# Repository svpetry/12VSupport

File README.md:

# 12VSupport
System to support a vehicle 12V electrical system with a LiIon battery to prevent the lead battery from depletion.

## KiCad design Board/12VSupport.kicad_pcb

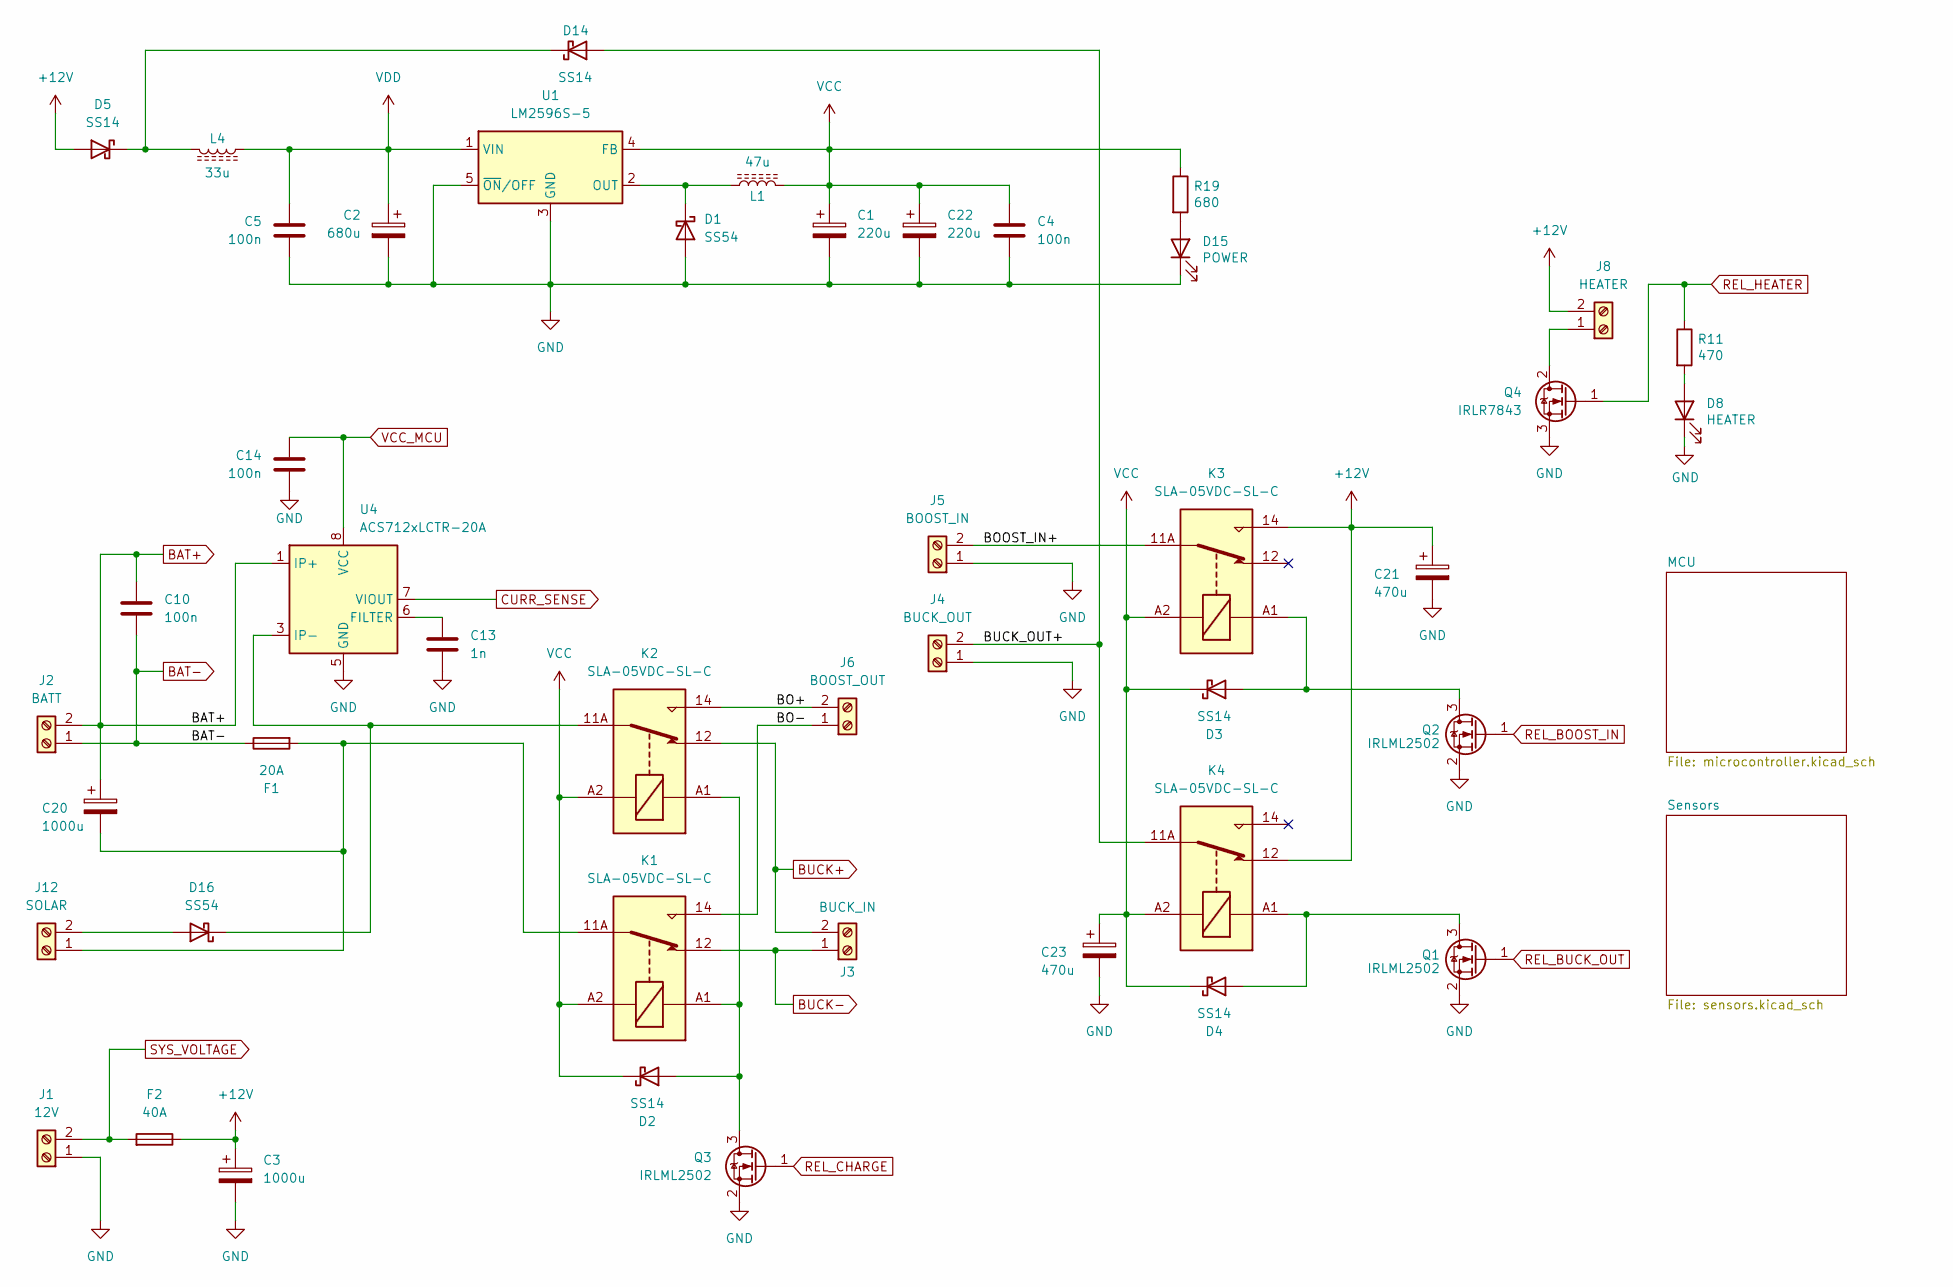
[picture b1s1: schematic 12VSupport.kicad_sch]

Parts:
C1, C22: 220u; CP_Radial_D6.3mm_P2.50mm
C2: 680u; CP_Radial_D10.0mm_P5.00mm
C3, C20: 1000u; CP_Radial_D13.0mm_P5.00mm
C4, C5, C10, C14: 100n; C_0805_2012Metric
C13: 1n; C_0805_2012Metric
C21: 470u; CP_Radial_D10.0mm_P5.00mm
C23: 470u; CP_Radial_D8.0mm_P3.80mm
D1, D16: SS54; D_SMB
D2, D3, D4, D5, D14: SS14; D_SMA
D8: HEATER; LED_0805_2012Metric
D15: POWER; LED_0805_2012Metric
F1: 20A; Fuseholder_Blade
F2: 40A; Fuseholder_Blade
J1: 12V; KF7.62_2P
J2: BATT; KF7.62_2P
J3: BUCK_IN; KF7.62_2P
J4: BUCK_OUT; KF7.62_2P
J5: BOOST_IN; KF7.62_2P
J6: BOOST_OUT; KF7.62_2P
J8: HEATER; TerminalBlock_Altech_AK300-2_P5.00mm
J12: SOLAR; TerminalBlock_Altech_AK300-2_P5.00mm
K1, K2, K3, K4: SLA-05VDC-SL-C; Relay_SPDT_RAYEX-L90
L1: 47u; L_12x12mm_H6mm
L4: 33u; L_10.4x10.4_H4.8
Q1, Q2, Q3: IRLML2502; SOT-23
Q4: IRLR7843; TO-252-2
R11: 470; R_0805_2012Metric
R19: 680; R_0805_2012Metric
U1: LM2596S-5; TO-263-5_TabPin3
U4: ACS712xLCTR-20A; SOIC-8_3.9x4.9mm_P1.27mm

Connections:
+12V: C3.1, C21.1, D5.2 (A), F2.1, J8.2, K3.14, K4.12
/BO+: J6.2, K2.14
/BO-: J6.1, K1.14
/BOOST_IN+: J5.2, K3.11A, K3.11B
/BUCK_OUT+: D14.2 (A), J4.2, K4.11A, K4.11B
BAT+: C10.1, C20.1, J2.2, U4.1 (IP+), U4.2 (IP+); also elsewhere on the board
BAT-: C10.2, F1.1, J2.1; also elsewhere on the board
BUCK+: J3.2, K2.12
BUCK-: J3.1, K1.12
CURR_SENSE: U4.7 (VIOUT); also elsewhere on the board
GND: C1.2, C2.2, C3.2, C4.2, C5.2, C13.2, C14.2, C21.2, C22.2, C23.2, D1.2 (A), D8.1 (K), D15.1 (K), J1.1, J4.1, J5.1, Q1.2 (S), Q2.2 (S), Q3.2 (S), Q4.3 (S), U1.3 (GND), U1.5 (~ON/OFF), U4.5 (GND); also elsewhere on the board
unnamed: D1.1 (K), L1.1, U1.2 (OUT)
unnamed: D2.2 (A), K1.A1, K2.A1, Q3.3 (D)
unnamed: D3.2 (A), K3.A1, Q2.3 (D)
unnamed: D4.2 (A), K4.A1, Q1.3 (D)
unnamed: D8.2 (A), R11.2
unnamed: D5.1 (K), D14.1 (K), L4.2
unnamed: D15.2 (A), R19.2
unnamed: D16.2 (A), J12.2
unnamed: D16.1 (K), K2.11A, K2.11B, U4.3 (IP-), U4.4 (IP-)
unnamed: J8.1, Q4.2 (D)
unnamed: C20.2, F1.2, J12.1, K1.11A, K1.11B
unnamed: C13.1, U4.6 (FILTER)
REL_BOOST_IN: Q2.1 (G); also elsewhere on the board
REL_BUCK_OUT: Q1.1 (G); also elsewhere on the board
REL_CHARGE: Q3.1 (G); also elsewhere on the board
REL_HEATER: Q4.1 (G), R11.1; also elsewhere on the board
SYS_VOLTAGE: F2.2, J1.2; also elsewhere on the board
VCC: C1.1, C4.1, C22.1, C23.1, D2.1 (K), D3.1 (K), D4.1 (K), K1.A2, K2.A2, K3.A2, K4.A2, L1.2, R19.1, U1.4 (FB); also elsewhere on the board
VCC_MCU: C14.1, U4.8 (VCC); also elsewhere on the board
VDD: C2.1, C5.1, L4.1, U1.1 (VIN); also elsewhere on the board

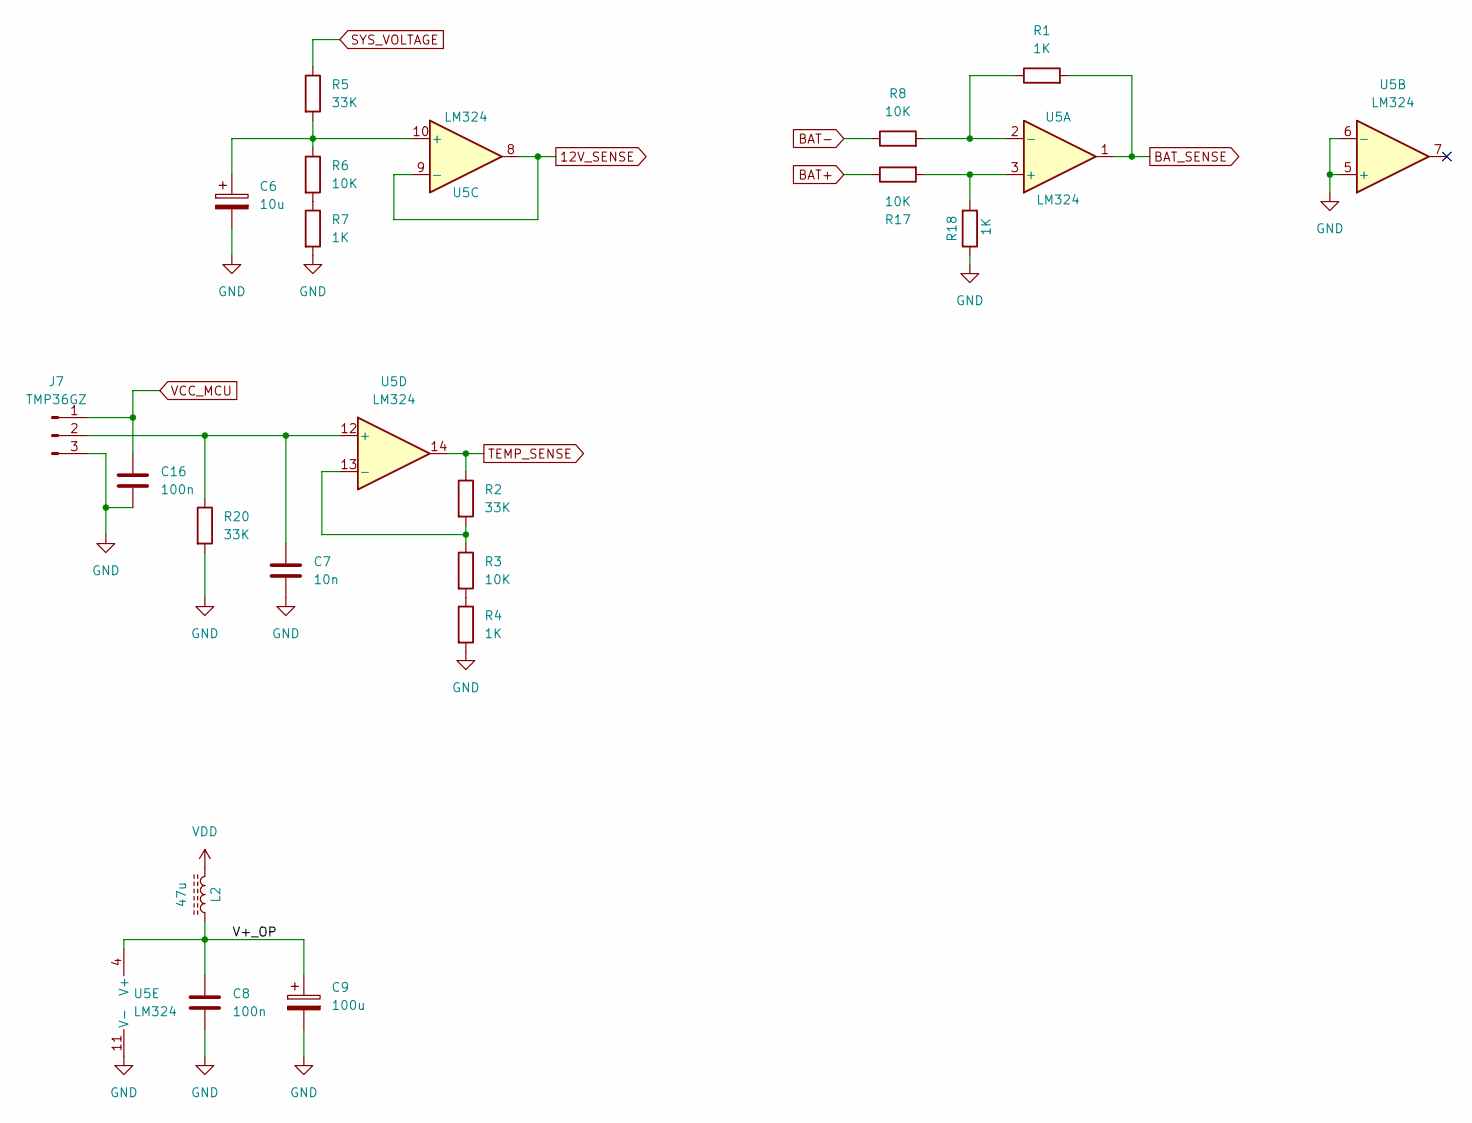
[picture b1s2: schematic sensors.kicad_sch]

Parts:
C6: 10u; C_1206_3216Metric_Pad1.33x1.80mm_HandSolder
C7: 10n; C_0805_2012Metric
C8, C16: 100n; C_0805_2012Metric
C9: 100u; CP_Radial_D5.0mm_P2.50mm
J7: TMP36GZ; JST_PH_B3B-PH-K_1x03_P2.00mm_Vertical
L2: 47u; L_10.4x10.4_H4.8
R1, R4, R7, R18: 1K; R_0805_2012Metric
R2, R5, R20: 33K; R_0805_2012Metric
R3, R6, R8, R17: 10K; R_0805_2012Metric
U5: LM324; SOIC-14_3.9x8.7mm_P1.27mm

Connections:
12V_SENSE: U5.8, U5.9 (-); also elsewhere on the board
/Sensors/V+_OP: C8.1, C9.1, L2.1, U5.4 (V+)
BAT+: R17.1; also elsewhere on the board
BAT-: R8.1; also elsewhere on the board
BAT_SENSE: R1.2, U5.1; also elsewhere on the board
GND: C6.2, C7.2, C8.2, C9.2, C16.2, J7.3, R4.2, R7.2, R18.1, R20.2, U5.5 (+), U5.6 (-), U5.11 (V-); also elsewhere on the board
unnamed: C7.1, J7.2, R20.1, U5.12 (+)
unnamed: R3.2, R4.1
unnamed: R6.2, R7.1
unnamed: R17.2, R18.2, U5.3 (+)
unnamed: R1.1, R8.2, U5.2 (-)
unnamed: C6.1, R5.2, R6.1, U5.10 (+)
unnamed: R2.2, R3.1, U5.13 (-)
SYS_VOLTAGE: R5.1; also elsewhere on the board
TEMP_SENSE: R2.1, U5.14; also elsewhere on the board
VCC_MCU: C16.1, J7.1; also elsewhere on the board
VDD: L2.2; also elsewhere on the board

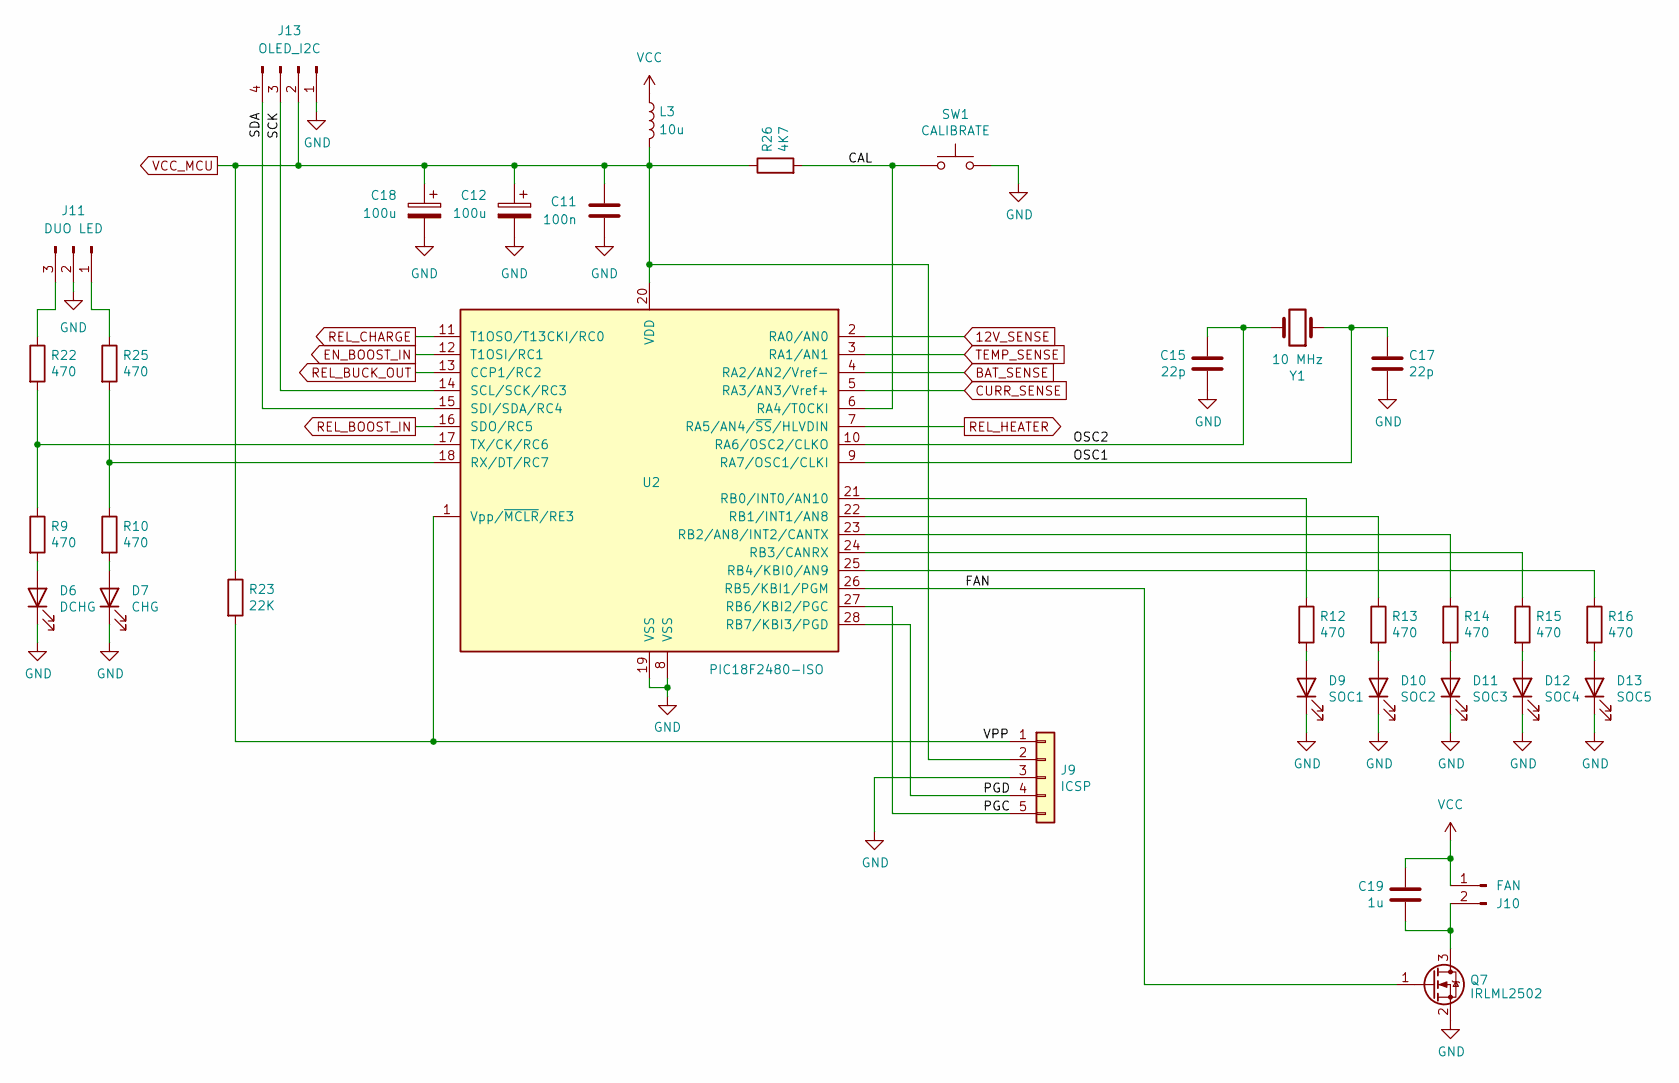
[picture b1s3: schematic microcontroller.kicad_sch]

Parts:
C11: 100n; C_0805_2012Metric
C12, C18: 100u; CP_Radial_D5.0mm_P2.50mm
C15, C17: 22p; C_0805_2012Metric
C19: 1u; C_1206_3216Metric
D6: DCHG; LED_0805_2012Metric
D7: CHG; LED_0805_2012Metric
D9: SOC1; LED_0805_2012Metric
D10: SOC2; LED_0805_2012Metric
D11: SOC3; LED_0805_2012Metric
D12: SOC4; LED_0805_2012Metric
D13: SOC5; LED_0805_2012Metric
J9: ICSP; PinHeader_1x05_P2.54mm_Vertical
J10: FAN; JST_XH_B2B-XH-A_1x02_P2.50mm_Vertical
J11: DUO LED; JST_PH_B3B-PH-K_1x03_P2.00mm_Vertical
J13: OLED_I2C; JST_PH_B4B-PH-K_1x04_P2.00mm_Vertical
L3: 10u; CD43
Q7: IRLML2502; SOT-23
R9, R10, R12, R13, R14, R15, R16, R22, R25: 470; R_0805_2012Metric
R23: 22K; R_0805_2012Metric
R26: 4K7; R_0805_2012Metric
SW1: CALIBRATE; SW_SPST_CK_RS282G05A3
U2: PIC18F2480-ISO; SOIC-28W_7.5x17.9mm_P1.27mm
Y1: 10 MHz; Crystal_HC18-U_Vertical

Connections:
12V_SENSE: U2.2 (RA0/AN0); also elsewhere on the board
/MCU/CAL: R26.2, SW1.1, U2.6 (RA4/T0CKI)
/MCU/FAN: Q7.1 (G), U2.26 (RB5/KBI1/PGM)
/MCU/OSC1: C17.1, U2.9 (RA7/OSC1/CLKI), Y1.1
/MCU/OSC2: C15.1, U2.10 (RA6/OSC2/CLKO), Y1.2
/MCU/PGC: J9.5, U2.27 (RB6/KBI2/PGC)
/MCU/PGD: J9.4, U2.28 (RB7/KBI3/PGD)
/MCU/SCK: J13.3, U2.14 (SCL/SCK/RC3)
/MCU/SDA: J13.4, U2.15 (SDI/SDA/RC4)
/MCU/VPP: J9.1, R23.2, U2.1 (Vpp/~MCLR/RE3)
BAT_SENSE: U2.4 (RA2/AN2/Vref-); also elsewhere on the board
CURR_SENSE: U2.5 (RA3/AN3/Vref+); also elsewhere on the board
EN_BOOST_IN: U2.12 (T1OSI/RC1)
GND: C11.2, C12.2, C15.2, C17.2, C18.2, D6.1 (K), D7.1 (K), D9.1 (K), D10.1 (K), D11.1 (K), D12.1 (K), D13.1 (K), J9.3, J11.2, J13.1, Q7.2 (S), SW1.2, U2.8 (VSS), U2.19 (VSS); also elsewhere on the board
unnamed: D6.2 (A), R9.2
unnamed: D7.2 (A), R10.2
unnamed: D9.2 (A), R12.2
unnamed: D10.2 (A), R13.2
unnamed: D11.2 (A), R14.2
unnamed: D12.2 (A), R15.2
unnamed: D13.2 (A), R16.2
unnamed: C19.2, J10.2, Q7.3 (D)
unnamed: J11.1, R25.1
unnamed: J11.3, R22.1
unnamed: R12.1, U2.21 (RB0/INT0/AN10)
unnamed: R13.1, U2.22 (RB1/INT1/AN8)
unnamed: R14.1, U2.23 (RB2/AN8/INT2/CANTX)
unnamed: R15.1, U2.24 (RB3/CANRX)
unnamed: R16.1, U2.25 (RB4/KBI0/AN9)
unnamed: R10.1, R25.2, U2.18 (RX/DT/RC7)
unnamed: R9.1, R22.2, U2.17 (TX/CK/RC6)
REL_BOOST_IN: U2.16 (SDO/RC5); also elsewhere on the board
REL_BUCK_OUT: U2.13 (CCP1/RC2); also elsewhere on the board
REL_CHARGE: U2.11 (T1OSO/T13CKI/RC0); also elsewhere on the board
REL_HEATER: U2.7 (RA5/AN4/~SS/HLVDIN); also elsewhere on the board
TEMP_SENSE: U2.3 (RA1/AN1); also elsewhere on the board
VCC: C19.1, J10.1, L3.1; also elsewhere on the board
VCC_MCU: C11.1, C12.1, C18.1, J9.2, J13.2, L3.2, R23.1, R26.1, U2.20 (VDD); also elsewhere on the board

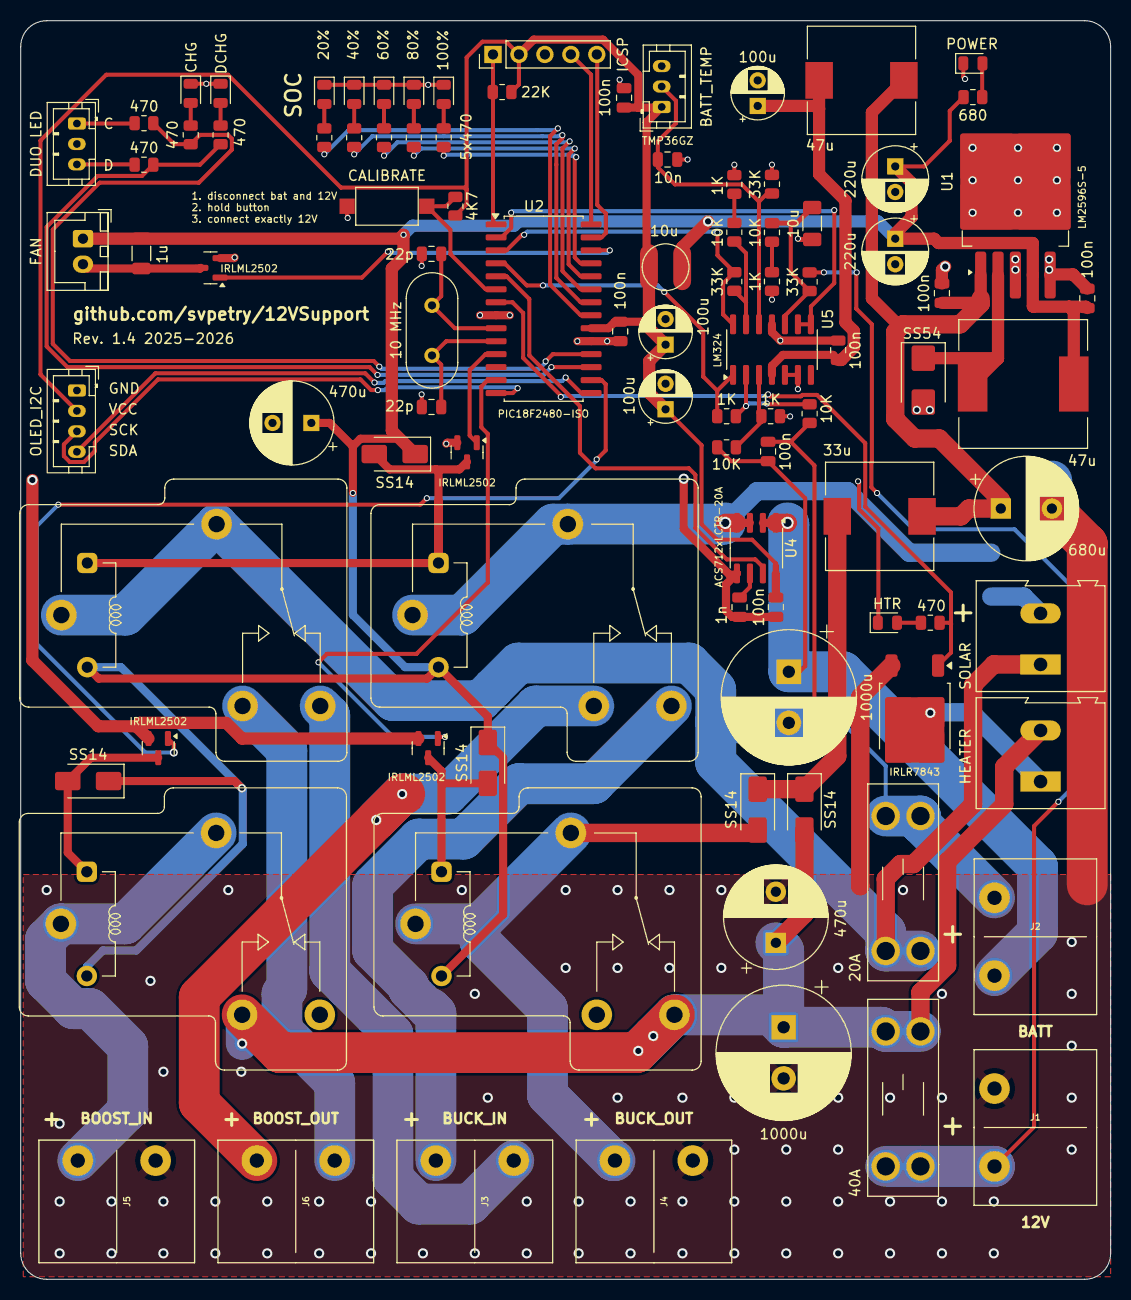
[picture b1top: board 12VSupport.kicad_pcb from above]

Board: 2 copper layers, 106.7 x 123.2 mm, 97 parts (1 on the bottom side), 68 nets.

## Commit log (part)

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2024-11-30 MCU project: initial commit.
2024-11-30 Rename VPP signal
2024-11-30 Added main file, added config bits.
2024-11-30 Change fuse holders.
2024-11-30 MCU code WIP
2024-12-01 Fixes current sensor
2024-12-01 Detect missing battery.
2024-12-01 Remove diode in MCU supply line so MCU has full 5V.
2024-12-02 Added ground plane.
2024-12-08 MCU: Save calculated full capacity to EEPROM.
2024-12-08 Board WIP
2024-12-11 Rev 1.0
2024-12-14 MCU WIP
2024-12-14 Layout improvements. Set version to 1.1
2024-12-20 Fixes AD read bug.
2024-12-21 Schematic fixes
2024-12-21 Fixes temperature calculation
2024-12-21 MCU improvements
2024-12-21 Fixes battery voltage sensing.
2024-12-31 Schematic/layout improvements.
2024-12-31 1.1 improvements
2025-01-05 Minor improvements
2025-01-05 Larger screw terminals.
2025-01-05 Update date
2025-01-05 Rev. 1.1
2025-01-11 Refactoring
2025-01-11 Silkscreen fix
2025-01-11 Bugfixes
2025-01-12 Add constants for LiIon 10s battery.
2025-01-12 LiFePO4 capacity 40AH
2025-01-12 Bugfix in capacity calculation
2025-01-25 Set version number to 1.2. Various fixes. Add fan connector.
2025-01-25 Adds connector for external duo LED
2025-01-26 Changed battery temp sensor connector.
2025-01-29 Change fan connector.
2025-02-08 New layout
2025-02-08 Minor layout changes
2025-02-08 Rev. 1.2
2025-02-08 Remove boost converter input MOSFET
2025-02-22 Fix calibration.
2025-03-02 Kicad 9.0
2025-03-02 Fixes fan. Sets max battery temp to 50 degC.
2025-03-03 Bugfixes. Highest SOC led is now blinking when charging.
2025-03-03 Bugfixes & improvements
2025-03-06 Fixes SOC led bug.
2025-03-06 Workaround for relais problems.
2025-03-06 Adds wait.
2025-03-07 Kicad 9.0 migration
2025-04-17 Bugfixes. Improvements
2025-06-04 Changes voltage levels
2025-06-14 Replace unsigned char with uint8_t
2026-06-06 Saved with new KiCad version.
2026-06-07 - REL_HEATER is now RA5 (was RC3) - REL_BOOST_IN is now RC5 (was RC4) Add I2C OLED display connector Add AGENTS.md
2026-06-07 Add OLED battery status display
2026-06-07 Update project files
2026-06-07 Show CALIBRATING on display
2026-06-07 Bump version to 1.4
2026-06-18 Board: Small schematic layout changes
2026-06-18 Add battery temperature to OLed display
